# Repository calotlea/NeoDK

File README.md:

# NeoDK
An electrostimulation machine development kit.

## Overview
### What is it?
This project describes the design and implementation of a bare-bones, yet innovative and powerful, pulse-based electrostimulation device. Both its hardware and its firmware are open for modification and extension.

### Authors
Discord: @Onwrikbaar<br/>
E: <onwrikbaar@hotmail.com>

KiCad port: 
 * [Lea Calot](mailto:lea_calot@protonmail.ch), Discord @lea_calot<br/>, [@CalotLea](https://twitter.com/CalotLea)

### Status
This is a work in progress. The repo will be updated every few weeks until well into 2024.

### Goals
1. The last quarter century, innovation in the e-stim realm has been virtually nonexistent, despite massive advances in electronics and cheap computing power. Currently available commercial devices are without exception channel-oriented and produce TENS-like waveforms. The time has come to get rid of those historical remnants.
2. It is fairly easy for non-programmers to create, share and improve routines to be played on stereostim setups. Currently there is no way to achieve the same for pulse-based e-stim devices. This project aims to (eventually) bridge that gap.

### Disclaimer
NeoDK is experimental, recreational, educational hardware and software. It comes with absolutely no warranty of any kind. Its designs are free to use - under the conditions set forth in its [Licence](LICENSE.txt). Using the designs -in original or modified form- implies acceptance of any and all associated risks and liabilities.

### How (not) to use NeoDK
- Use it entirely at your own risk.
- Do not use it for anything time-critical, safety-critical, medical, industrial, military, commercial, or illegal - it was not designed for any of that.
- Do not use it on anyone without explicit and informed consent.
- Keep any and all electrodes connected to this device placed below the waist.
- Do not use a so-called triphase cable with this device!

### Safety
The NeoDK device can generate potentially lethal voltages and currents on its outputs and on internal components, even when powered from a battery. The risks associated with building, testing and using this device can be reduced but not eliminated.

The NeoDK device is designed to stay well within the IEC 60601-2-10 requirements. However, these limits are not necessarily maintained when the supply voltage, circuit, components or accompanying firmware are changed in any way.

### Audience
This project is intended for experienced electronics hobbyists and professionals, who possess a keen understanding of the risks associated with electrostimulation and high-voltage circuitry, and who desire one or more of the following:
- a deeper understanding of advanced electronic circuitry for pulse-based electrostimulation.
- an innovative, rock solid and well-tested design to base one's own developments on.
- a high-intensity remotely controllable e-stim device to incorporate into a multi-toy setup.
- e-stim sensations unattainable through conventional power boxes.
- a pulse-based device that can store and play user-created routines (planned for 2025).

### Caveat
NeoDK is a minimal viable design (MVD) of a powerful and highly efficient electrostimulation device that is not limited by 2-pole 'channels' or strictly TENS-like waveforms. It can thus do things no commercially available e-stim box comes close to. If this appeals to you but you still would like to have more features than NeoDK offers, by all means use NeoDK as the foundation for your own design - while observing this project's [Licence](LICENSE.txt). Regarding licensing for commercial / non-open source purposes, please contact the author.

### Why to start simple
"A complex system that works is invariably found to have evolved from a simple system that worked. A complex system designed from scratch never works and cannot be patched up to make it work. You have to start over with a working simple system." -- John Gall

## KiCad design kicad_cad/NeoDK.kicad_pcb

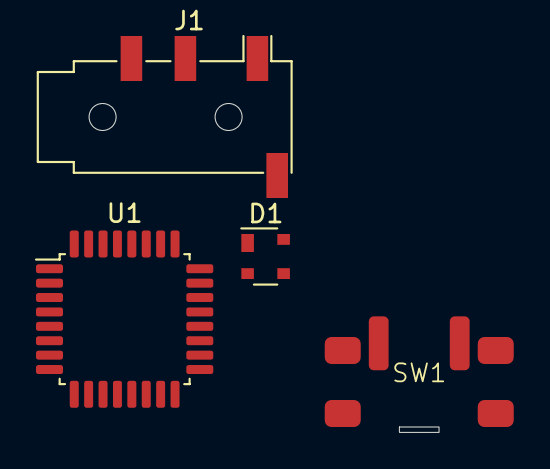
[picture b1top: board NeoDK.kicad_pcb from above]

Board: 2 copper layers, 4 parts (0 on the bottom side), 3 nets, no tracks yet.

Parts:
D1: PRTR5V0U2X; SOT-143
J1: PJ320D; Jack_3.5mm_PJ320D_Horizontal
SW1: TS-1045AD
U1: STM32G071KBTx; LQFP-32_7x7mm_P0.8mm

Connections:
/RXD_IN: D1.3 (I/O2), J1.T, U1.10 (PA3)
/TXD_OUT: D1.2 (I/O1), U1.9 (PA2)
GND: D1.1 (GND), SW1.3, SW1.4, SW1.5, SW1.6

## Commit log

2023-12-12 WiP Schematic

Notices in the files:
parts and their libraries:
License: CERN-OHL-W-2.0 license
